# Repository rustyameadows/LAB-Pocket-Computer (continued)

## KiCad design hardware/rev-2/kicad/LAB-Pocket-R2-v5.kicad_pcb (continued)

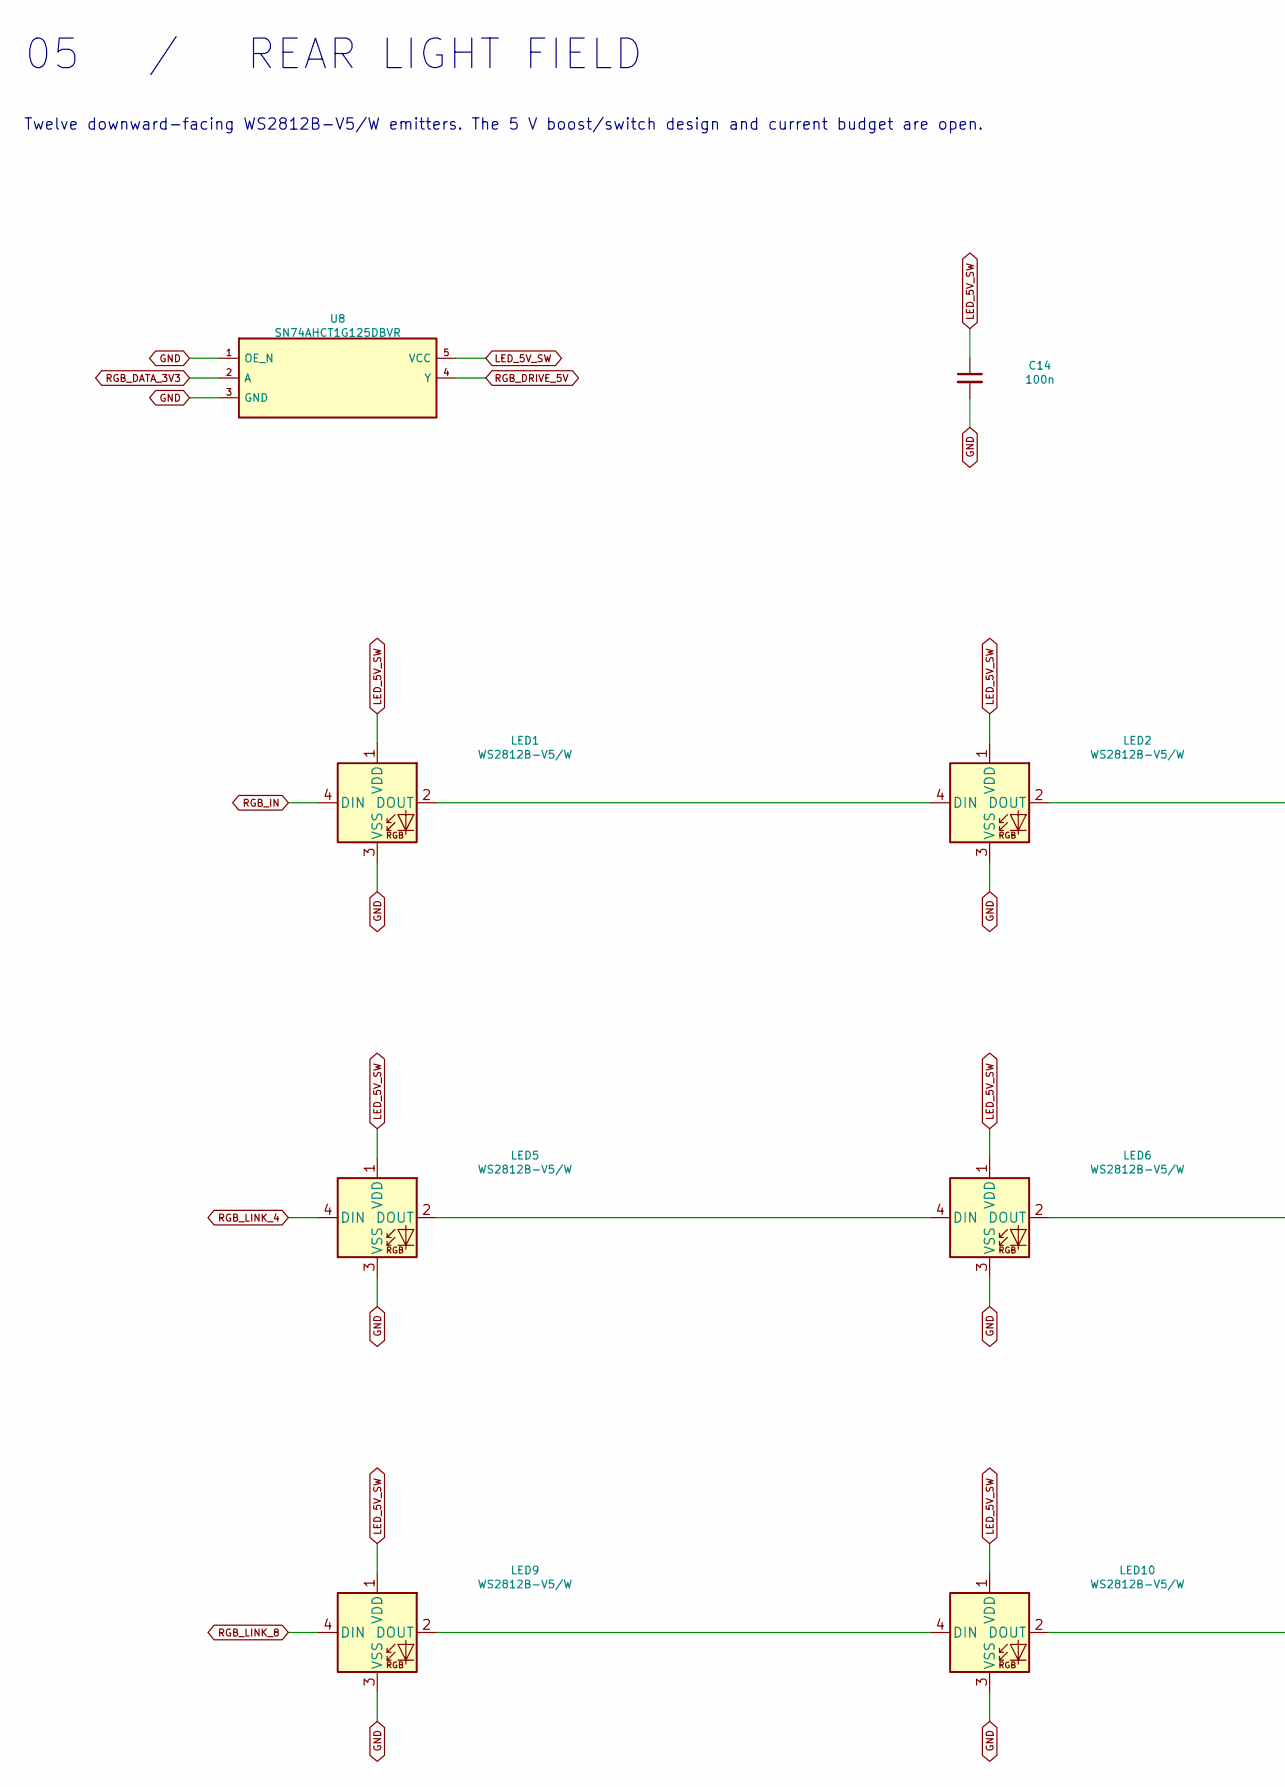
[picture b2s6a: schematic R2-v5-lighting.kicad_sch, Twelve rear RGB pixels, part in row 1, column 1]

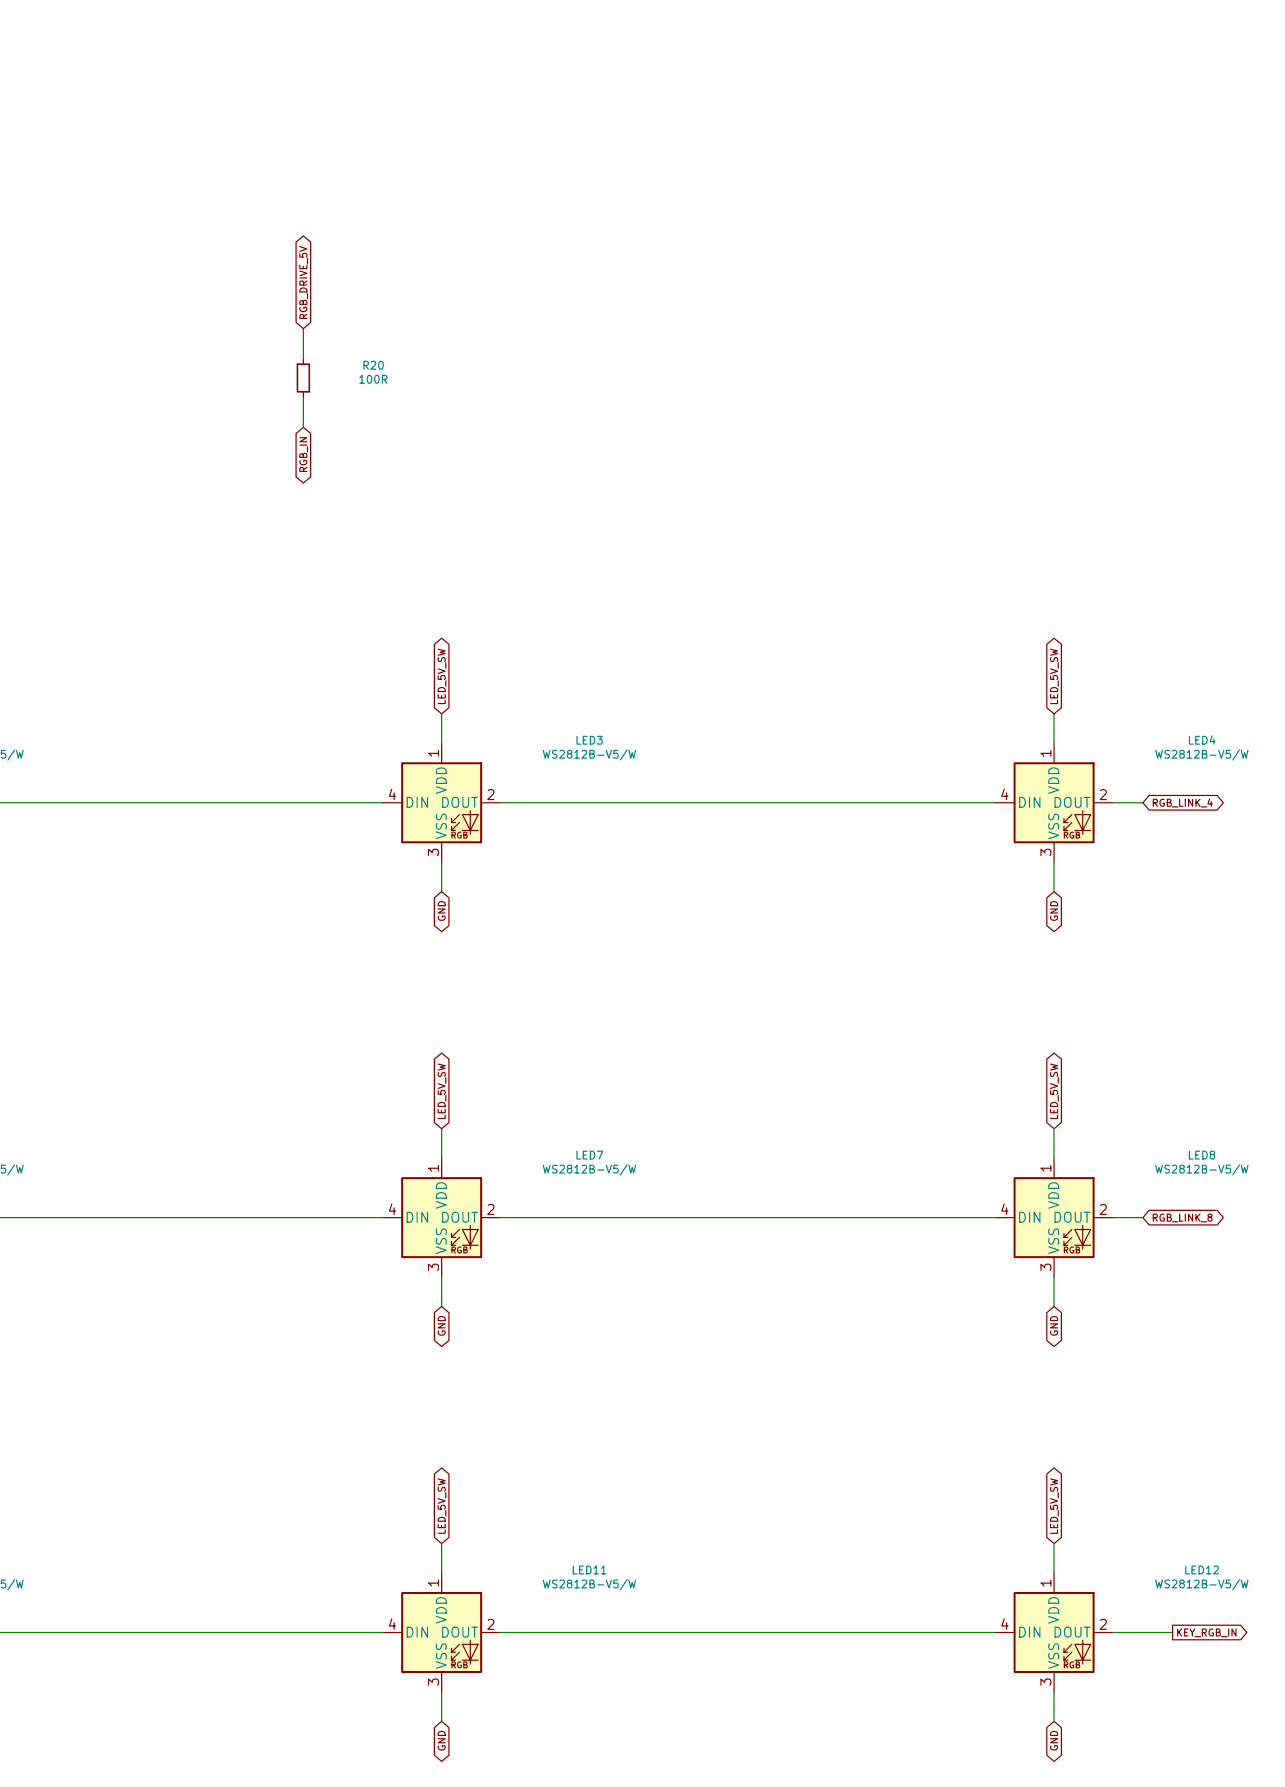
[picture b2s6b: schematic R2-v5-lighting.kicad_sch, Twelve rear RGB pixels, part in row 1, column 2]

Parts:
C14: 100n; C_0603_1608Metric; MPN C0603C104K5RACTU
LED1, LED2, LED3, LED4, LED5, LED6, LED7, LED8, LED9, LED10, LED11, LED12: WS2812B-V5/W; LED_WS2812B_PLCC4_5.0x5.0mm_P3.2mm; MPN WS2812B-V5/W
R20: 100R; R_0603_1608Metric; MPN CRCW0603100RFKEA
U8: SN74AHCT1G125DBVR; SOT-23-5; MPN SN74AHCT1G125DBVR

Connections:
GND: C14.2, LED1.3 (VSS), LED2.3 (VSS), LED3.3 (VSS), LED4.3 (VSS), LED5.3 (VSS), LED6.3 (VSS), LED7.3 (VSS), LED8.3 (VSS), LED9.3 (VSS), LED10.3 (VSS), LED11.3 (VSS), LED12.3 (VSS), U8.1 (OE_N), U8.3 (GND); also elsewhere on the board
KEY_RGB_IN: LED12.2 (DOUT); also elsewhere on the board
LED_5V_SW: C14.1, LED1.1 (VDD), LED2.1 (VDD), LED3.1 (VDD), LED4.1 (VDD), LED5.1 (VDD), LED6.1 (VDD), LED7.1 (VDD), LED8.1 (VDD), LED9.1 (VDD), LED10.1 (VDD), LED11.1 (VDD), LED12.1 (VDD), U8.5 (VCC); also elsewhere on the board
unnamed: LED1.2 (DOUT), LED2.4 (DIN)
unnamed: LED2.2 (DOUT), LED3.4 (DIN)
unnamed: LED3.2 (DOUT), LED4.4 (DIN)
unnamed: LED5.2 (DOUT), LED6.4 (DIN)
unnamed: LED6.2 (DOUT), LED7.4 (DIN)
unnamed: LED7.2 (DOUT), LED8.4 (DIN)
unnamed: LED9.2 (DOUT), LED10.4 (DIN)
unnamed: LED10.2 (DOUT), LED11.4 (DIN)
unnamed: LED11.2 (DOUT), LED12.4 (DIN)
RGB_DATA_3V3: U8.2 (A); also elsewhere on the board
RGB_DRIVE_5V: R20.1, U8.4 (Y)
RGB_IN: LED1.4 (DIN), R20.2
RGB_LINK_4: LED4.2 (DOUT), LED5.4 (DIN)
RGB_LINK_8: LED8.2 (DOUT), LED9.4 (DIN)

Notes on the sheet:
05 / REAR LIGHT FIELD
Twelve downward-facing WS2812B-V5/W emitters. The 5 V boost/switch design and current budget are open.

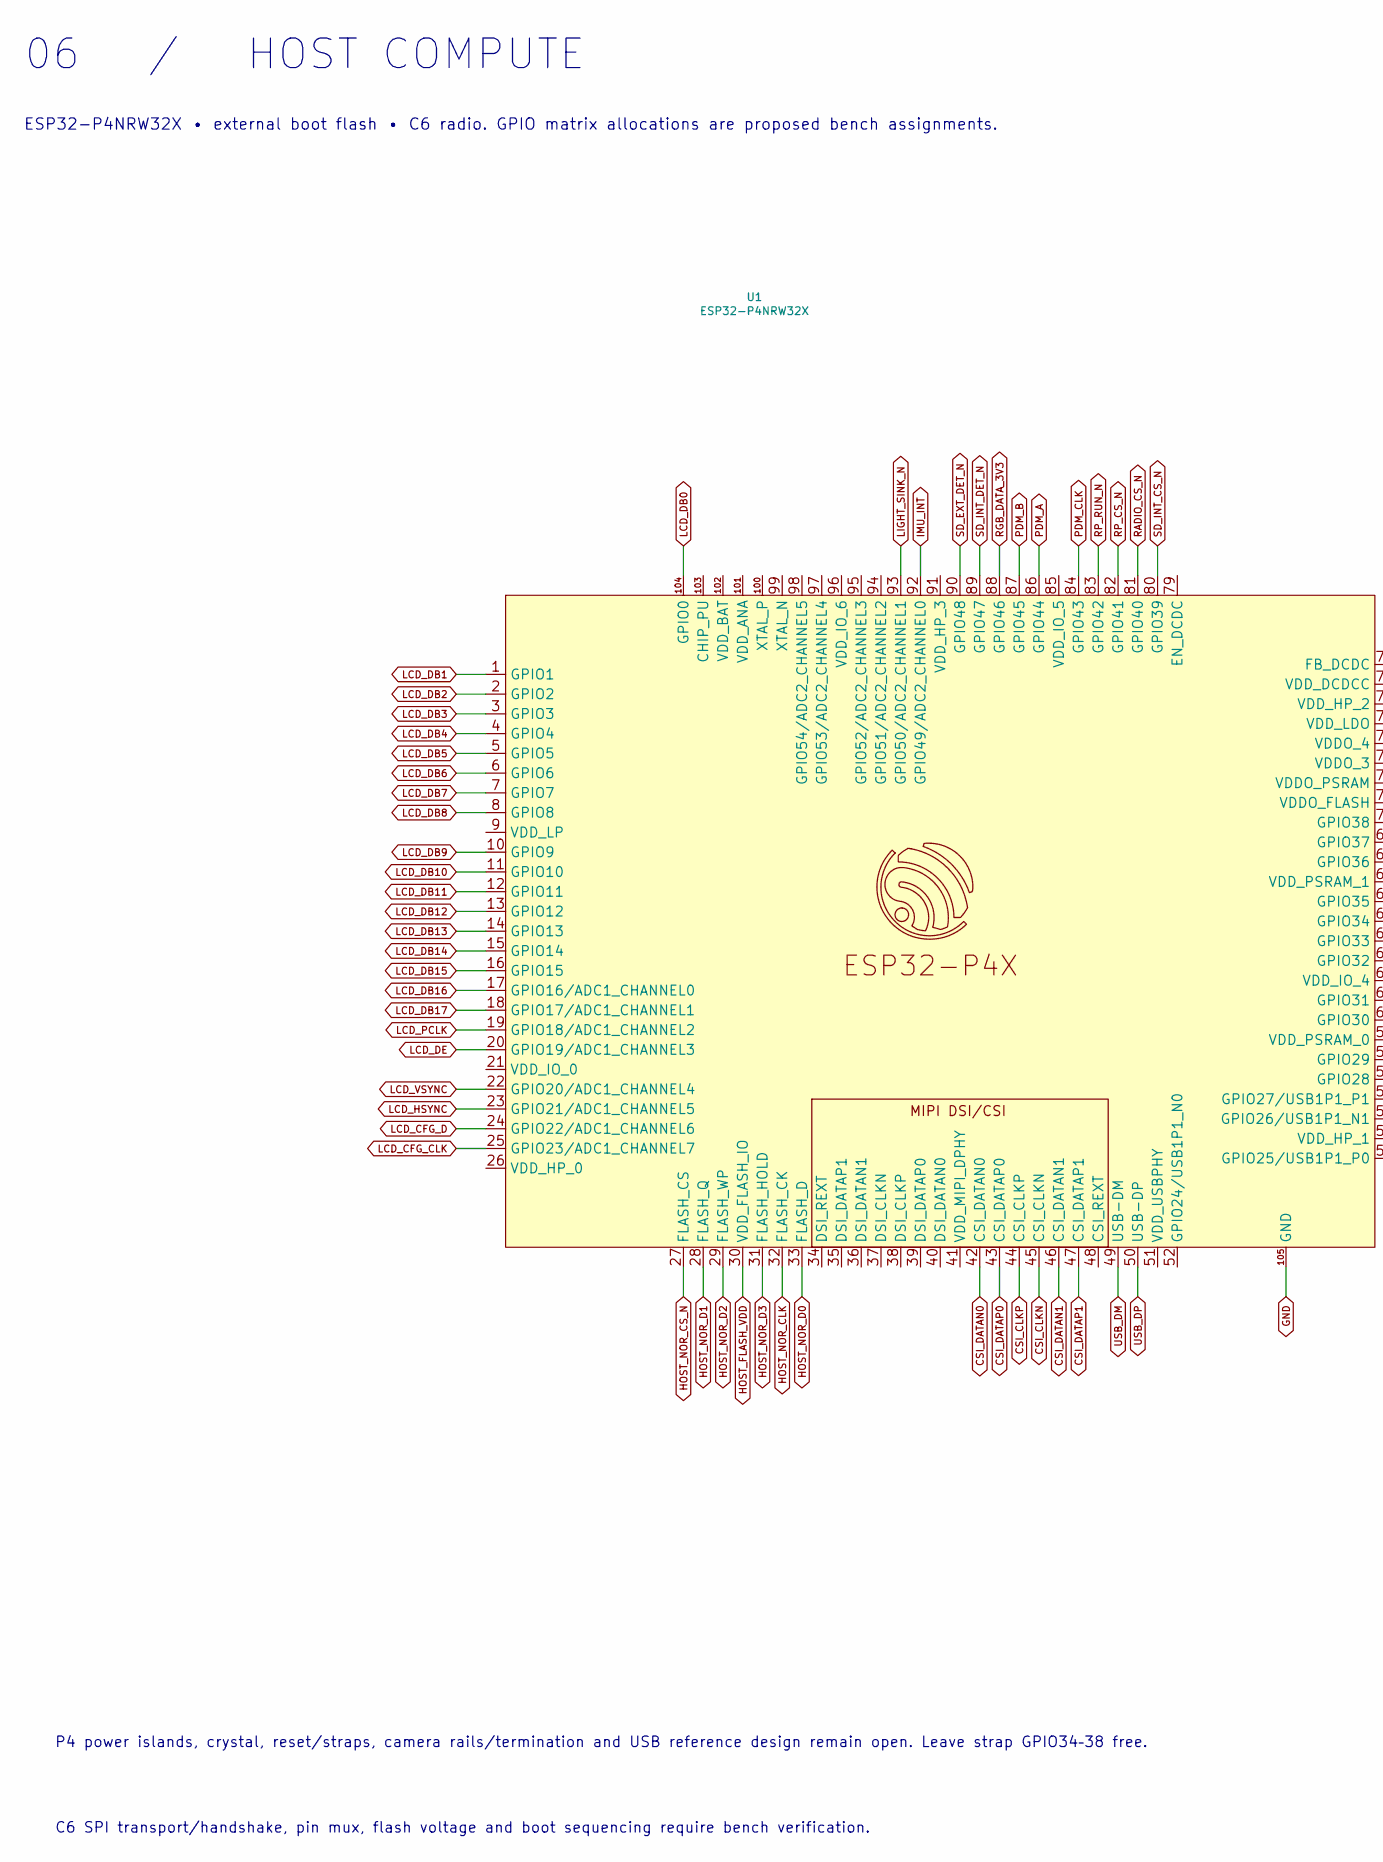
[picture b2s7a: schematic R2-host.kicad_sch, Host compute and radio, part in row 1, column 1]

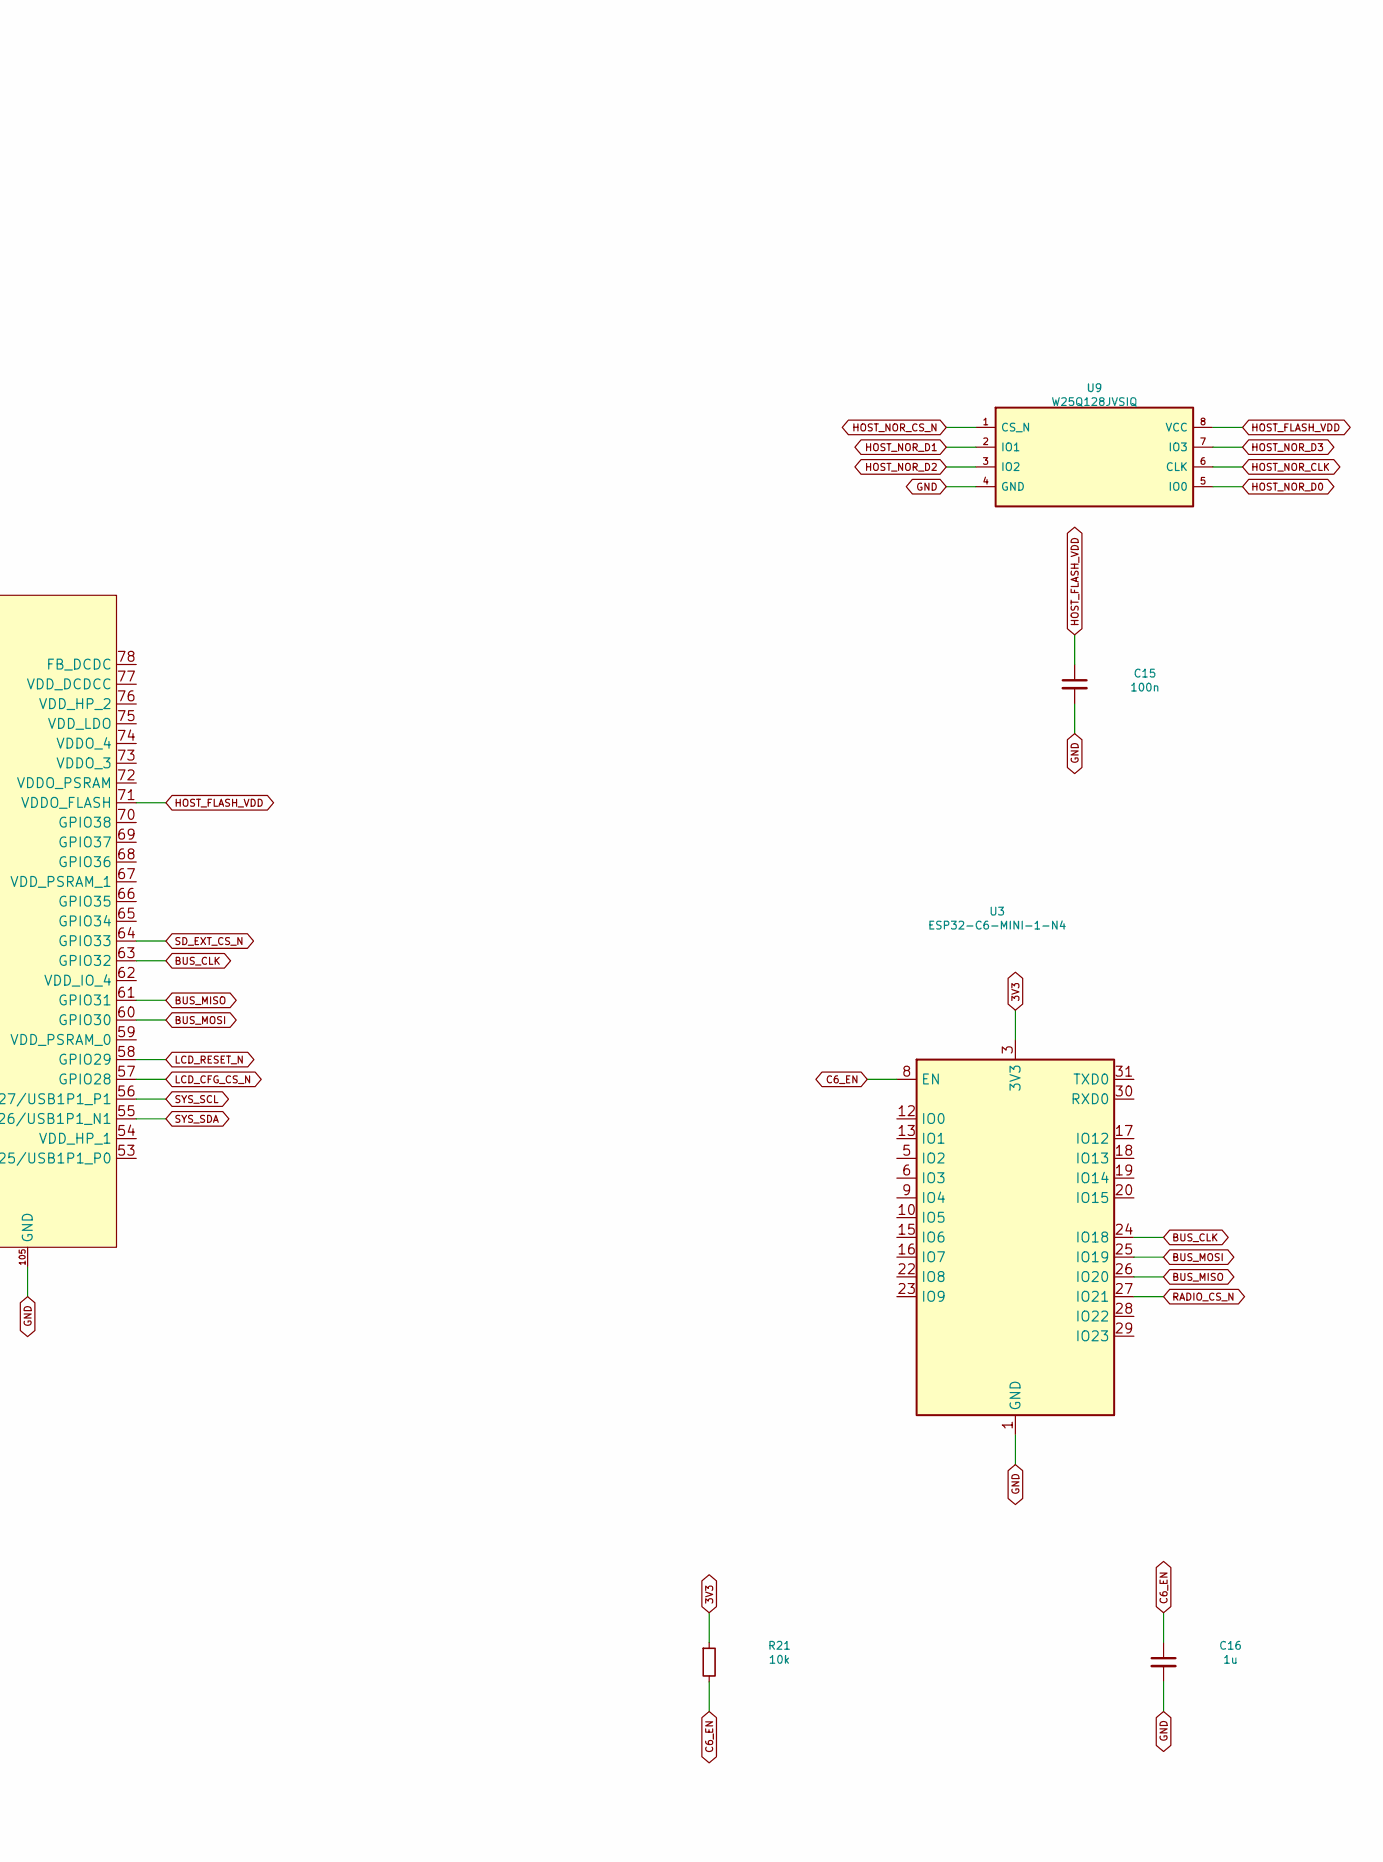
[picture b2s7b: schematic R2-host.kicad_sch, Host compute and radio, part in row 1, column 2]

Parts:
C15: 100n; C_0603_1608Metric; MPN C0603C104K5RACTU
C16: 1u; C_0603_1608Metric; MPN C0603C105K8PACTU
R21: 10k; R_0603_1608Metric; MPN CRCW060310K0FKEA
U1: ESP32-P4NRW32X; ESP32-P4; MPN ESP32-P4NRW32X
U3: ESP32-C6-MINI-1-N4; ESP32-C6-MINI-1; MPN ESP32-C6-MINI-1-N4
U9: W25Q128JVSIQ; SOIC-8_5.3x5.3mm_P1.27mm; MPN W25Q128JVSIQ

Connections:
3V3: R21.1, U3.3 (3V3); also elsewhere on the board
BUS_CLK: U1.63 (GPIO32), U3.24 (IO18); also elsewhere on the board
BUS_MISO: U1.61 (GPIO31), U3.26 (IO20); also elsewhere on the board
BUS_MOSI: U1.60 (GPIO30), U3.25 (IO19); also elsewhere on the board
C6_EN: C16.1, R21.2, U3.8 (EN)
CSI_CLKN: U1.45 (CSI_CLKN)
CSI_CLKP: U1.44 (CSI_CLKP)
CSI_DATAN0: U1.42 (CSI_DATAN0)
CSI_DATAN1: U1.46 (CSI_DATAN1)
CSI_DATAP0: U1.43 (CSI_DATAP0)
CSI_DATAP1: U1.47 (CSI_DATAP1)
GND: C15.2, C16.2, U1.105 (GND), U3.1 (GND), U3.2 (GND), U3.11 (GND), U3.14 (GND), U3.36 (GND), U3.37 (GND), U3.38 (GND), U3.39 (GND), U3.40 (GND), U3.41 (GND), U3.42 (GND), U3.43 (GND), U3.44 (GND), U3.45 (GND), U3.46 (GND), U3.47 (GND), U3.48 (GND), U3.49 (GND), U3.50 (GND), U3.51 (GND), U3.52 (GND), U3.53 (GND), U9.4 (GND); also elsewhere on the board
HOST_FLASH_VDD: C15.1, U1.30 (VDD_FLASH_IO), U1.71 (VDDO_FLASH), U9.8 (VCC)
HOST_NOR_CLK: U1.32 (FLASH_CK), U9.6 (CLK)
HOST_NOR_CS_N: U1.27 (FLASH_CS), U9.1 (CS_N)
HOST_NOR_D0: U1.33 (FLASH_D), U9.5 (IO0)
HOST_NOR_D1: U1.28 (FLASH_Q), U9.2 (IO1)
HOST_NOR_D2: U1.29 (FLASH_WP), U9.3 (IO2)
HOST_NOR_D3: U1.31 (FLASH_HOLD), U9.7 (IO3)
IMU_INT: U1.92 (GPIO49/ADC2_CHANNEL0); also elsewhere on the board
LCD_CFG_CLK: U1.25 (GPIO23/ADC1_CHANNEL7); also elsewhere on the board
LCD_CFG_CS_N: U1.57 (GPIO28); also elsewhere on the board
LCD_CFG_D: U1.24 (GPIO22/ADC1_CHANNEL6); also elsewhere on the board
LCD_DB0: U1.104 (GPIO0); also elsewhere on the board
LCD_DB1: U1.1 (GPIO1); also elsewhere on the board
LCD_DB2: U1.2 (GPIO2); also elsewhere on the board
LCD_DB3: U1.3 (GPIO3); also elsewhere on the board
LCD_DB4: U1.4 (GPIO4); also elsewhere on the board
LCD_DB5: U1.5 (GPIO5); also elsewhere on the board
LCD_DB6: U1.6 (GPIO6); also elsewhere on the board
LCD_DB7: U1.7 (GPIO7); also elsewhere on the board
LCD_DB8: U1.8 (GPIO8); also elsewhere on the board
LCD_DB9: U1.10 (GPIO9); also elsewhere on the board
LCD_DB10: U1.11 (GPIO10); also elsewhere on the board
LCD_DB11: U1.12 (GPIO11); also elsewhere on the board
LCD_DB12: U1.13 (GPIO12); also elsewhere on the board
LCD_DB13: U1.14 (GPIO13); also elsewhere on the board
LCD_DB14: U1.15 (GPIO14); also elsewhere on the board
LCD_DB15: U1.16 (GPIO15); also elsewhere on the board
LCD_DB16: U1.17 (GPIO16/ADC1_CHANNEL0); also elsewhere on the board
LCD_DB17: U1.18 (GPIO17/ADC1_CHANNEL1); also elsewhere on the board
LCD_DE: U1.20 (GPIO19/ADC1_CHANNEL3); also elsewhere on the board
LCD_HSYNC: U1.23 (GPIO21/ADC1_CHANNEL5); also elsewhere on the board
LCD_PCLK: U1.19 (GPIO18/ADC1_CHANNEL2); also elsewhere on the board
LCD_RESET_N: U1.58 (GPIO29); also elsewhere on the board
LCD_VSYNC: U1.22 (GPIO20/ADC1_CHANNEL4); also elsewhere on the board
LIGHT_SINK_N: U1.93 (GPIO50/ADC2_CHANNEL1); also elsewhere on the board
PDM_A: U1.86 (GPIO44); also elsewhere on the board
PDM_B: U1.87 (GPIO45); also elsewhere on the board
PDM_CLK: U1.84 (GPIO43); also elsewhere on the board
RADIO_CS_N: U1.81 (GPIO40), U3.27 (IO21)
RGB_DATA_3V3: U1.88 (GPIO46); also elsewhere on the board
RP_CS_N: U1.82 (GPIO41); also elsewhere on the board
RP_RUN_N: U1.83 (GPIO42); also elsewhere on the board
SD_EXT_CS_N: U1.64 (GPIO33); also elsewhere on the board
SD_EXT_DET_N: U1.90 (GPIO48); also elsewhere on the board
SD_INT_CS_N: U1.80 (GPIO39); also elsewhere on the board
SD_INT_DET_N: U1.89 (GPIO47); also elsewhere on the board
SYS_SCL: U1.56 (GPIO27/USB1P1_P1); also elsewhere on the board
SYS_SDA: U1.55 (GPIO26/USB1P1_N1); also elsewhere on the board
USB_DM: U1.49 (USB-DM); also elsewhere on the board
USB_DP: U1.50 (USB-DP); also elsewhere on the board

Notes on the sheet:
06 / HOST COMPUTE
ESP32-P4NRW32X • external boot flash • C6 radio. GPIO matrix allocations are proposed bench assignments.
P4 power islands, crystal, reset/straps, camera rails/termination and USB reference design remain open. Leave strap GPIO34–38 free.
C6 SPI transport/handshake, pin mux, flash voltage and boot sequencing require bench verification.

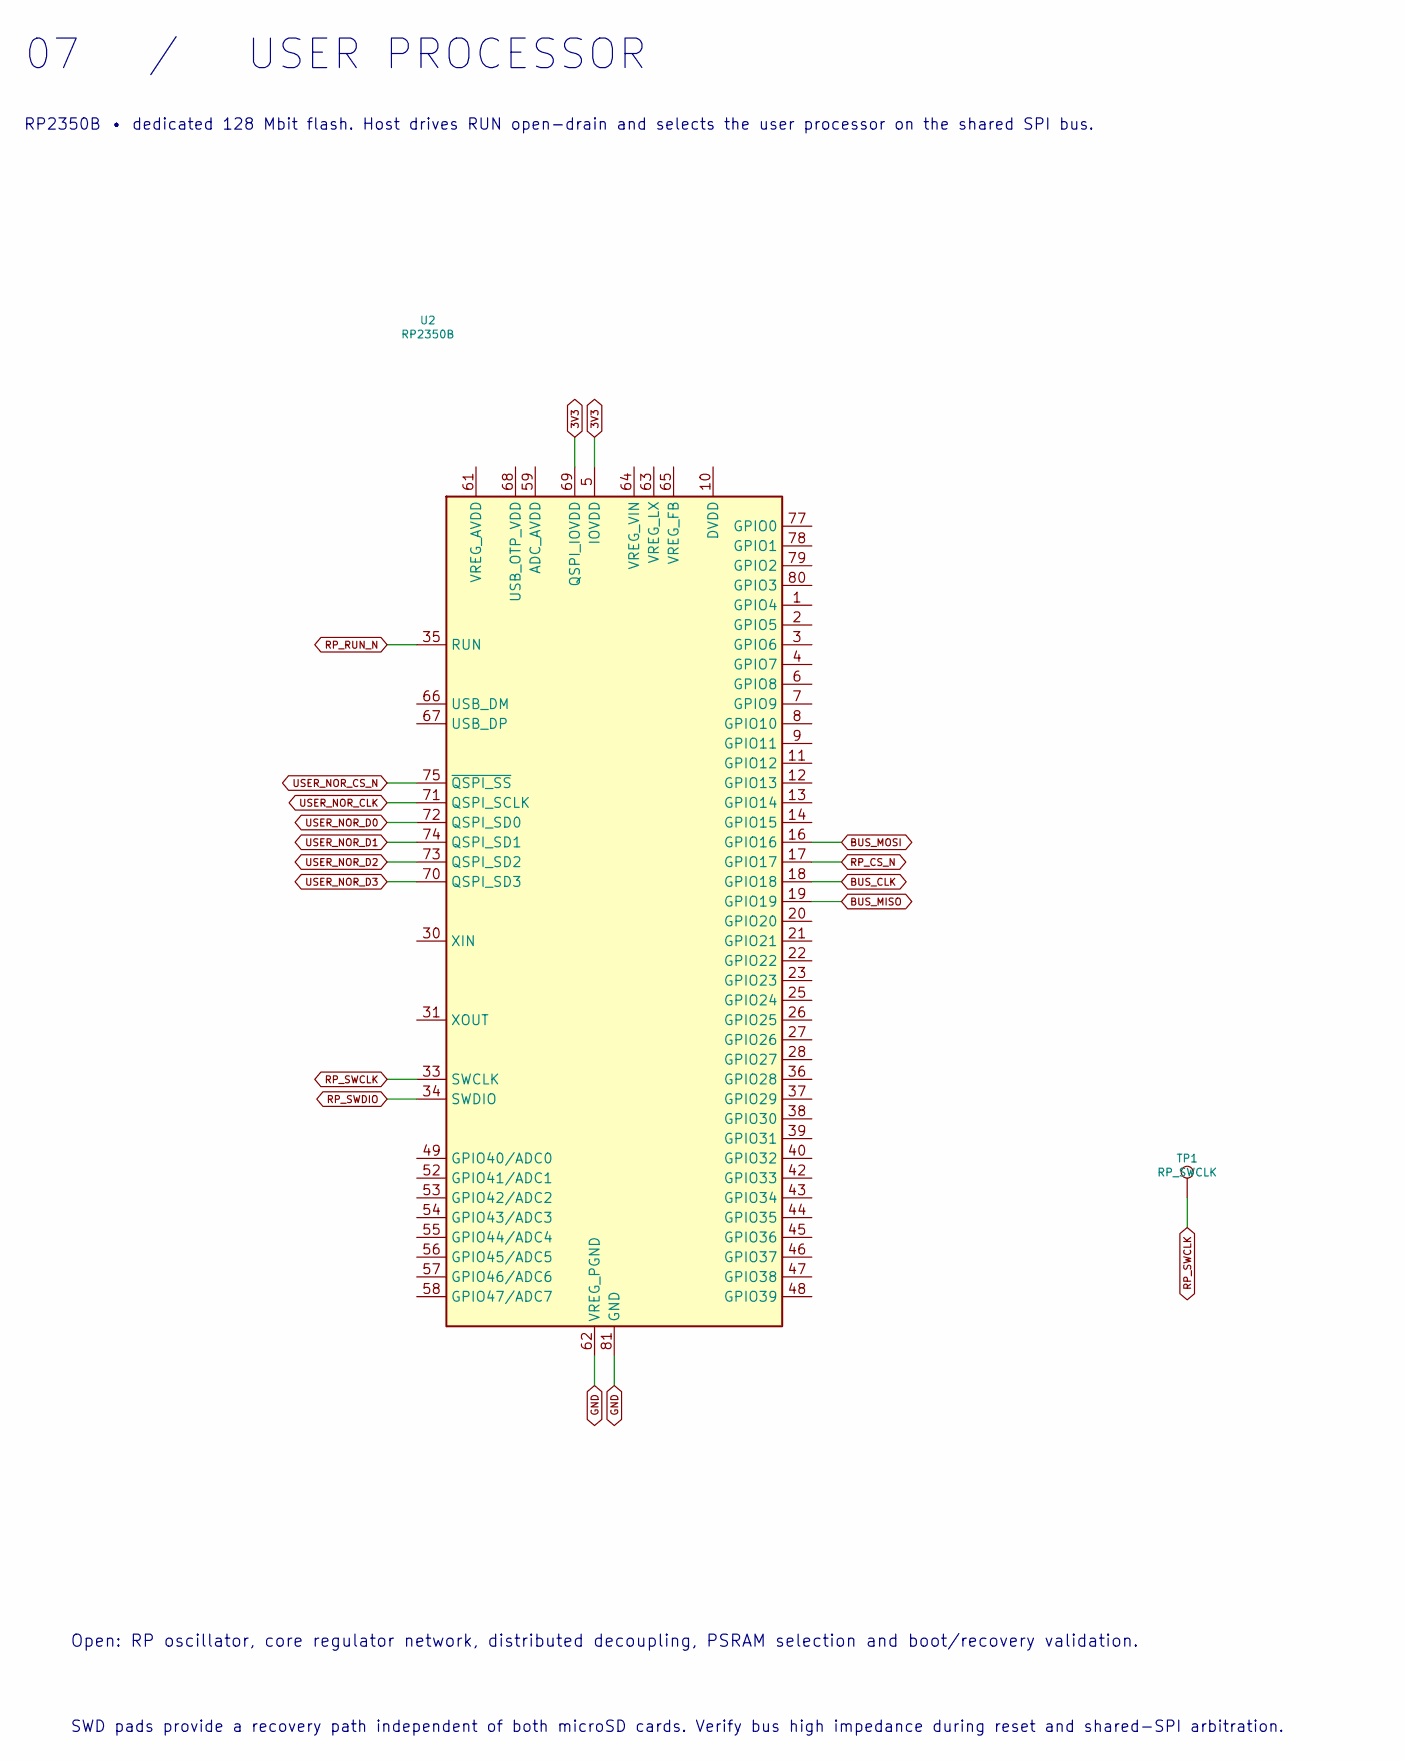
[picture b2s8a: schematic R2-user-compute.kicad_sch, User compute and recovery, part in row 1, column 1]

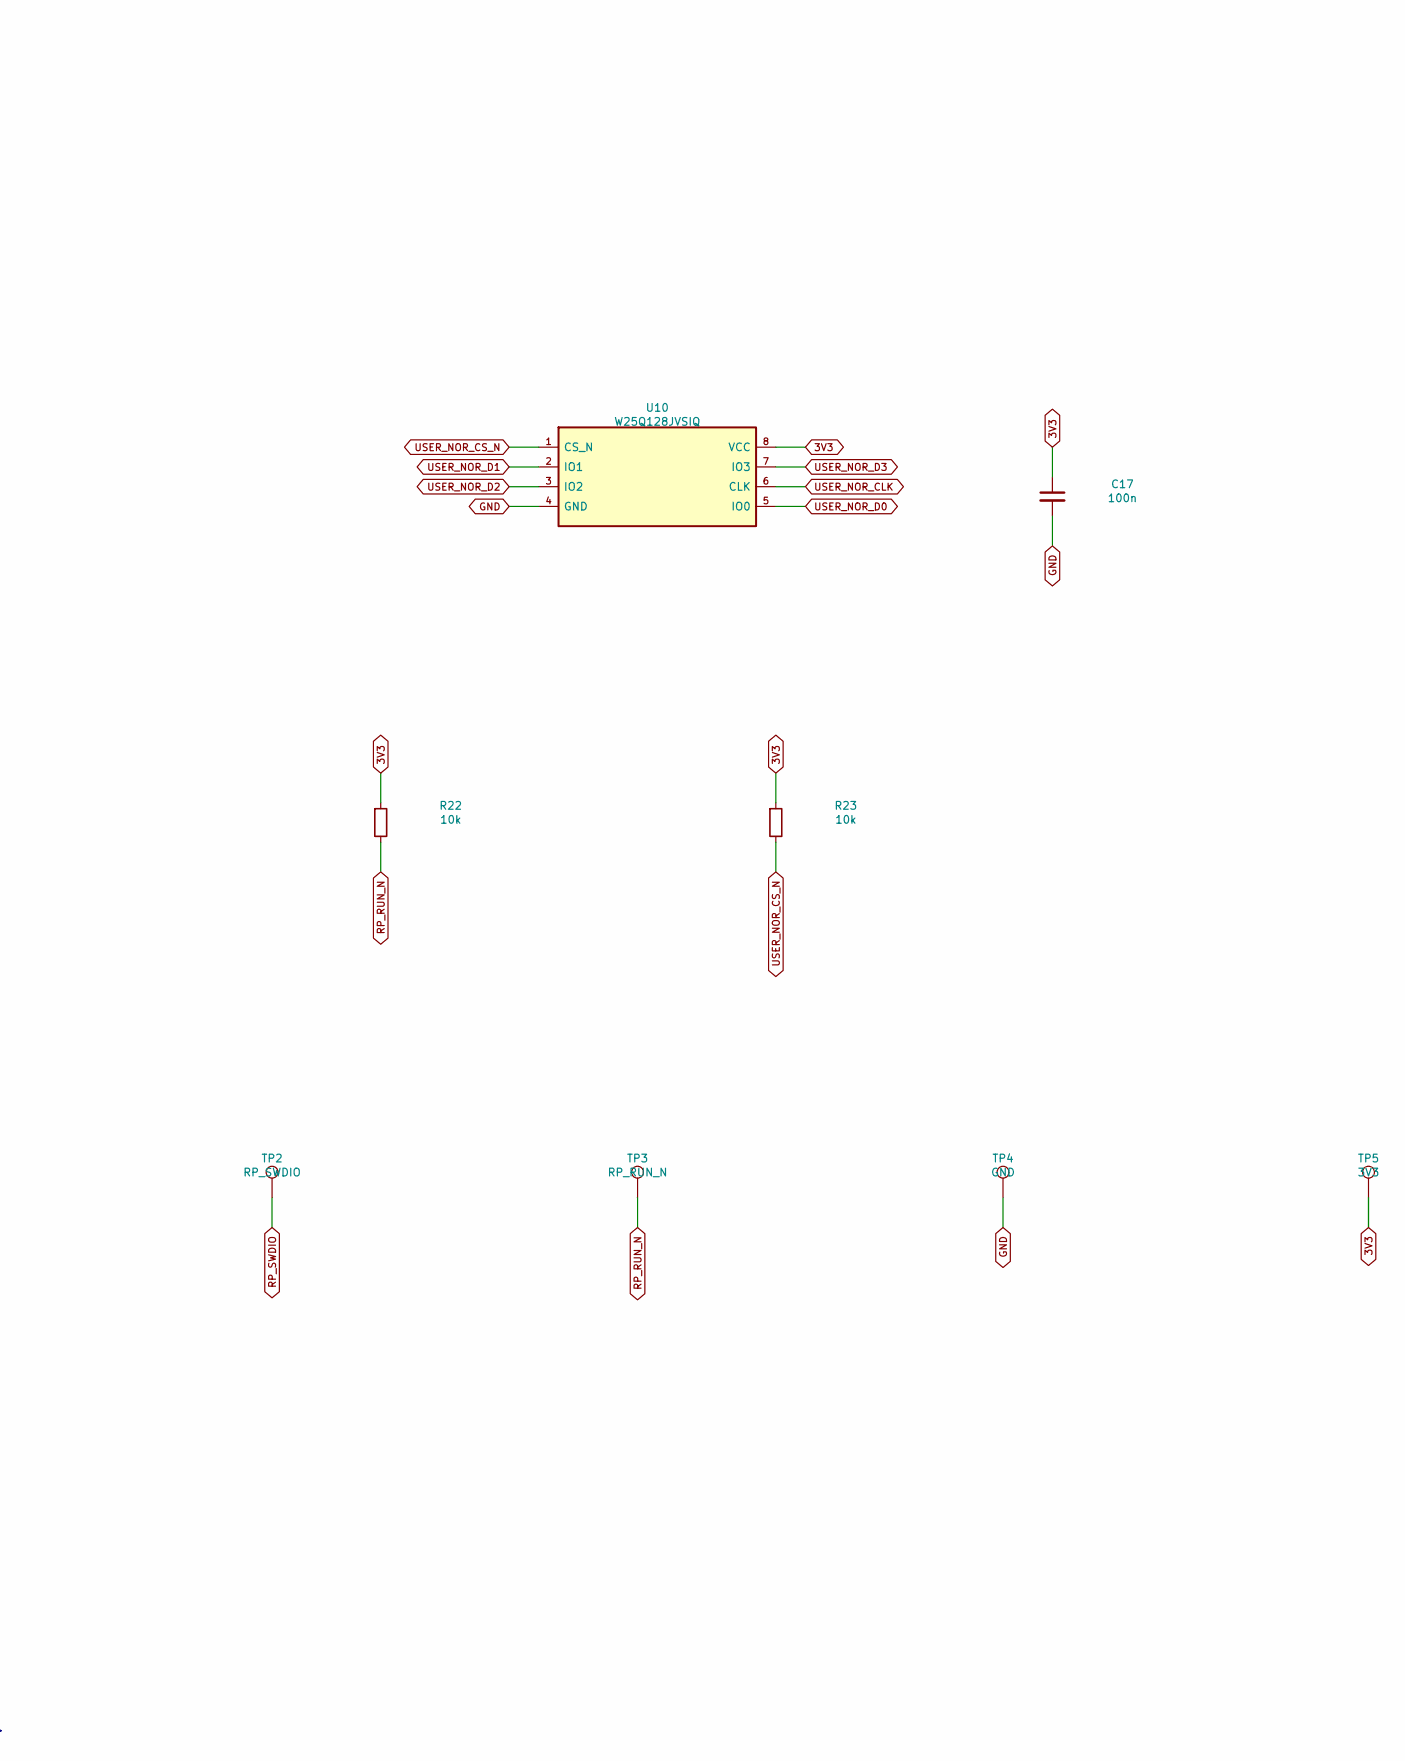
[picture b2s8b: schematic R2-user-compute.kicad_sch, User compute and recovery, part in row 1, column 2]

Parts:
C17: 100n; C_0603_1608Metric; MPN C0603C104K5RACTU
R22, R23: 10k; R_0603_1608Metric; MPN CRCW060310K0FKEA
TP1: RP_SWCLK; TestPoint_Pad_D1.0mm; MPN PCB feature
TP2: RP_SWDIO; TestPoint_Pad_D1.0mm; MPN PCB feature
TP3: RP_RUN_N; TestPoint_Pad_D1.0mm; MPN PCB feature
TP4: GND; TestPoint_Pad_D1.0mm; MPN PCB feature
TP5: 3V3; TestPoint_Pad_D1.0mm; MPN PCB feature
U2: RP2350B; QFN-80-1EP_10x10mm_P0.4mm_EP3.4x3.4mm; MPN RP2350B
U10: W25Q128JVSIQ; SOIC-8_5.3x5.3mm_P1.27mm; MPN W25Q128JVSIQ

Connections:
3V3: C17.1, R22.1, R23.1, TP5.1, U2.5 (IOVDD), U2.15 (IOVDD), U2.24 (IOVDD), U2.29 (IOVDD), U2.41 (IOVDD), U2.50 (IOVDD), U2.60 (IOVDD), U2.69 (QSPI_IOVDD), U2.76 (IOVDD), U10.8 (VCC); also elsewhere on the board
BUS_CLK: U2.18 (GPIO18); also elsewhere on the board
BUS_MISO: U2.19 (GPIO19); also elsewhere on the board
BUS_MOSI: U2.16 (GPIO16); also elsewhere on the board
GND: C17.2, TP4.1, U2.62 (VREG_PGND), U2.81 (GND), U10.4 (GND); also elsewhere on the board
unnamed: U2.10 (DVDD), U2.32 (DVDD), U2.51 (DVDD)
RP_CS_N: U2.17 (GPIO17); also elsewhere on the board
RP_RUN_N: R22.2, TP3.1, U2.35 (RUN); also elsewhere on the board
RP_SWCLK: TP1.1, U2.33 (SWCLK)
RP_SWDIO: TP2.1, U2.34 (SWDIO)
USER_NOR_CLK: U2.71 (QSPI_SCLK), U10.6 (CLK)
USER_NOR_CS_N: R23.2, U2.75 (~QSPI_SS), U10.1 (CS_N)
USER_NOR_D0: U2.72 (QSPI_SD0), U10.5 (IO0)
USER_NOR_D1: U2.74 (QSPI_SD1), U10.2 (IO1)
USER_NOR_D2: U2.73 (QSPI_SD2), U10.3 (IO2)
USER_NOR_D3: U2.70 (QSPI_SD3), U10.7 (IO3)

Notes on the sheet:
07 / USER PROCESSOR
RP2350B • dedicated 128 Mbit flash. Host drives RUN open-drain and selects the user processor on the shared SPI bus.
Open: RP oscillator, core regulator network, distributed decoupling, PSRAM selection and boot/recovery validation.
SWD pads provide a recovery path independent of both microSD cards. Verify bus high impedance during reset and shared-SPI arbitration.

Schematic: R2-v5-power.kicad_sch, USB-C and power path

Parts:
BT1: LP735977JH; MPN LP735977JH+PCM+2 WIRES 70MM
C18: 1u; C_0603_1608Metric; MPN C0603C105K8PACTU
C19, C20: 4.7u; C_0805_2012Metric; MPN C0805C475K8PACTU
J1: USB4110-GF-A; USB4110-v5; MPN USB4110-GF-A
J6: JST PH • keyed harness; JST_PH_S3B-PH-SM4-TB_1x03-1MP_P2.00mm_Horizontal; MPN S3B-PH-SM4-TB
R24, R25: 5.1k; R_0603_1608Metric; MPN CRCW06035K10FKEA
R26: 2.2k; R_0603_1608Metric; MPN CRCW06032K20FKEA
R27: 3.0k; R_0603_1608Metric; MPN CRCW06033K00FKEA
U11: BQ24074RGTR; VQFN-16-1EP_3x3mm_P0.5mm_EP1.6x1.6mm; MPN BQ24074RGTR

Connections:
CC1: J1.A5 (CC1), R24.1
CC2: J1.B5 (CC2), R25.1
CHG_ISET: R26.1, U11.16 (ISET)
GND: BT1.2 (PACK_NEG), C18.2, C19.2, C20.2, J1.A1 (GND), J1.A12 (GND), J1.B1 (GND), J1.B12 (GND), J1.SH (SHIELD), J6.1, R24.2, R25.2, R26.2, R27.2, U11.5 (EN2), U11.6 (EN1), U11.8 (VSS), U11.17 (VSS); also elsewhere on the board
ILIM_SET: R27.1, U11.12 (ILIM)
PACK_POS: BT1.1 (PACK_POS), C20.1, J6.3, U11.2 (BAT), U11.3 (BAT)
PACK_TS: J6.2, U11.1 (TS)
USB_DM: J1.A7 (D-), J1.B7 (D-); also elsewhere on the board
USB_DP: J1.A6 (D+), J1.B6 (D+); also elsewhere on the board
VBUS: C18.1, J1.A4 (VBUS), J1.A9 (VBUS), J1.B4 (VBUS), J1.B9 (VBUS), U11.13 (IN)
VSYS: C19.1, U11.4 (~CE), U11.10 (OUT), U11.11 (OUT)

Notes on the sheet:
08 / USB / POWER PATH
BQ24074 single-cell power path. Charging is held disabled for the first electrical review.
EN1=EN2=0 selects USB100. CE tracks OUT to inhibit charging. Two-wire battery requires a qualified external thermistor. J6 pin 1 = GND, 2 = TS, 3 = BAT+.
Review cable current, inrush, ESD, ISET, ILIM, temperature range and thermal layout before enabling charge. VSYS is an unregulated system output.
Unimplemented: VSYS to 3V3 buck-boost, LCD/backlight supply, switched LED 5 V, MCU core rails and fuel gauge.

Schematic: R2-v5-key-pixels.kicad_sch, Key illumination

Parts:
C21, C22, C23, C24, C25, C26, C27, C28, C29, C30, C31, C32, C33, C34, C35, C36: 100n; C_0402_1005Metric; MPN C0402C104K8RACTU
LED13, LED14, LED15, LED16, LED17, LED18, LED19, LED20, LED21, LED22, LED23, LED24, LED25, LED26, LED27, LED28: SK6805-EC10-000; SK6805-EC10-v5; MPN SK6805-EC10-000

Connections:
GND: C21.2, C22.2, C23.2, C24.2, C25.2, C26.2, C27.2, C28.2, C29.2, C30.2, C31.2, C32.2, C33.2, C34.2, C35.2, C36.2, LED13.1 (VSS), LED14.1 (VSS), LED15.1 (VSS), LED16.1 (VSS), LED17.1 (VSS), LED18.1 (VSS), LED19.1 (VSS), LED20.1 (VSS), LED21.1 (VSS), LED22.1 (VSS), LED23.1 (VSS), LED24.1 (VSS), LED25.1 (VSS), LED26.1 (VSS), LED27.1 (VSS), LED28.1 (VSS); also elsewhere on the board
KEY_RGB_01: LED13.4 (DOUT), LED14.2 (DIN)
KEY_RGB_02: LED14.4 (DOUT), LED15.2 (DIN)
KEY_RGB_03: LED15.4 (DOUT), LED16.2 (DIN)
KEY_RGB_04: LED16.4 (DOUT), LED17.2 (DIN)
KEY_RGB_05: LED17.4 (DOUT), LED18.2 (DIN)
KEY_RGB_06: LED18.4 (DOUT), LED19.2 (DIN)
KEY_RGB_07: LED19.4 (DOUT), LED20.2 (DIN)
KEY_RGB_08: LED20.4 (DOUT), LED21.2 (DIN)
KEY_RGB_09: LED21.4 (DOUT), LED22.2 (DIN)
KEY_RGB_10: LED22.4 (DOUT), LED23.2 (DIN)
KEY_RGB_11: LED23.4 (DOUT), LED24.2 (DIN)
KEY_RGB_12: LED24.4 (DOUT), LED25.2 (DIN)
KEY_RGB_13: LED25.4 (DOUT), LED26.2 (DIN)
KEY_RGB_14: LED26.4 (DOUT), LED27.2 (DIN)
KEY_RGB_15: LED27.4 (DOUT), LED28.2 (DIN)
KEY_RGB_IN: LED13.2 (DIN); also elsewhere on the board
LED_5V_SW: C21.1, C22.1, C23.1, C24.1, C25.1, C26.1, C27.1, C28.1, C29.1, C30.1, C31.1, C32.1, C33.1, C34.1, C35.1, C36.1, LED13.3 (VDD), LED14.3 (VDD), LED15.3 (VDD), LED16.3 (VDD), LED17.3 (VDD), LED18.3 (VDD), LED19.3 (VDD), LED20.3 (VDD), LED21.3 (VDD), LED22.3 (VDD), LED23.3 (VDD), LED24.3 (VDD), LED25.3 (VDD), LED26.3 (VDD), LED27.3 (VDD), LED28.3 (VDD); also elsewhere on the board

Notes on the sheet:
KEY ILLUMINATION
Front view, row-major key order. Pixel 01 receives the output of rear LED12. Each pixel has a local 100 nF bypass.
